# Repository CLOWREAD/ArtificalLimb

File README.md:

# ArtificalLimb
A repository to store data related to software and hardware design of a control card used to drive the solenoid for an artificial limb concept.

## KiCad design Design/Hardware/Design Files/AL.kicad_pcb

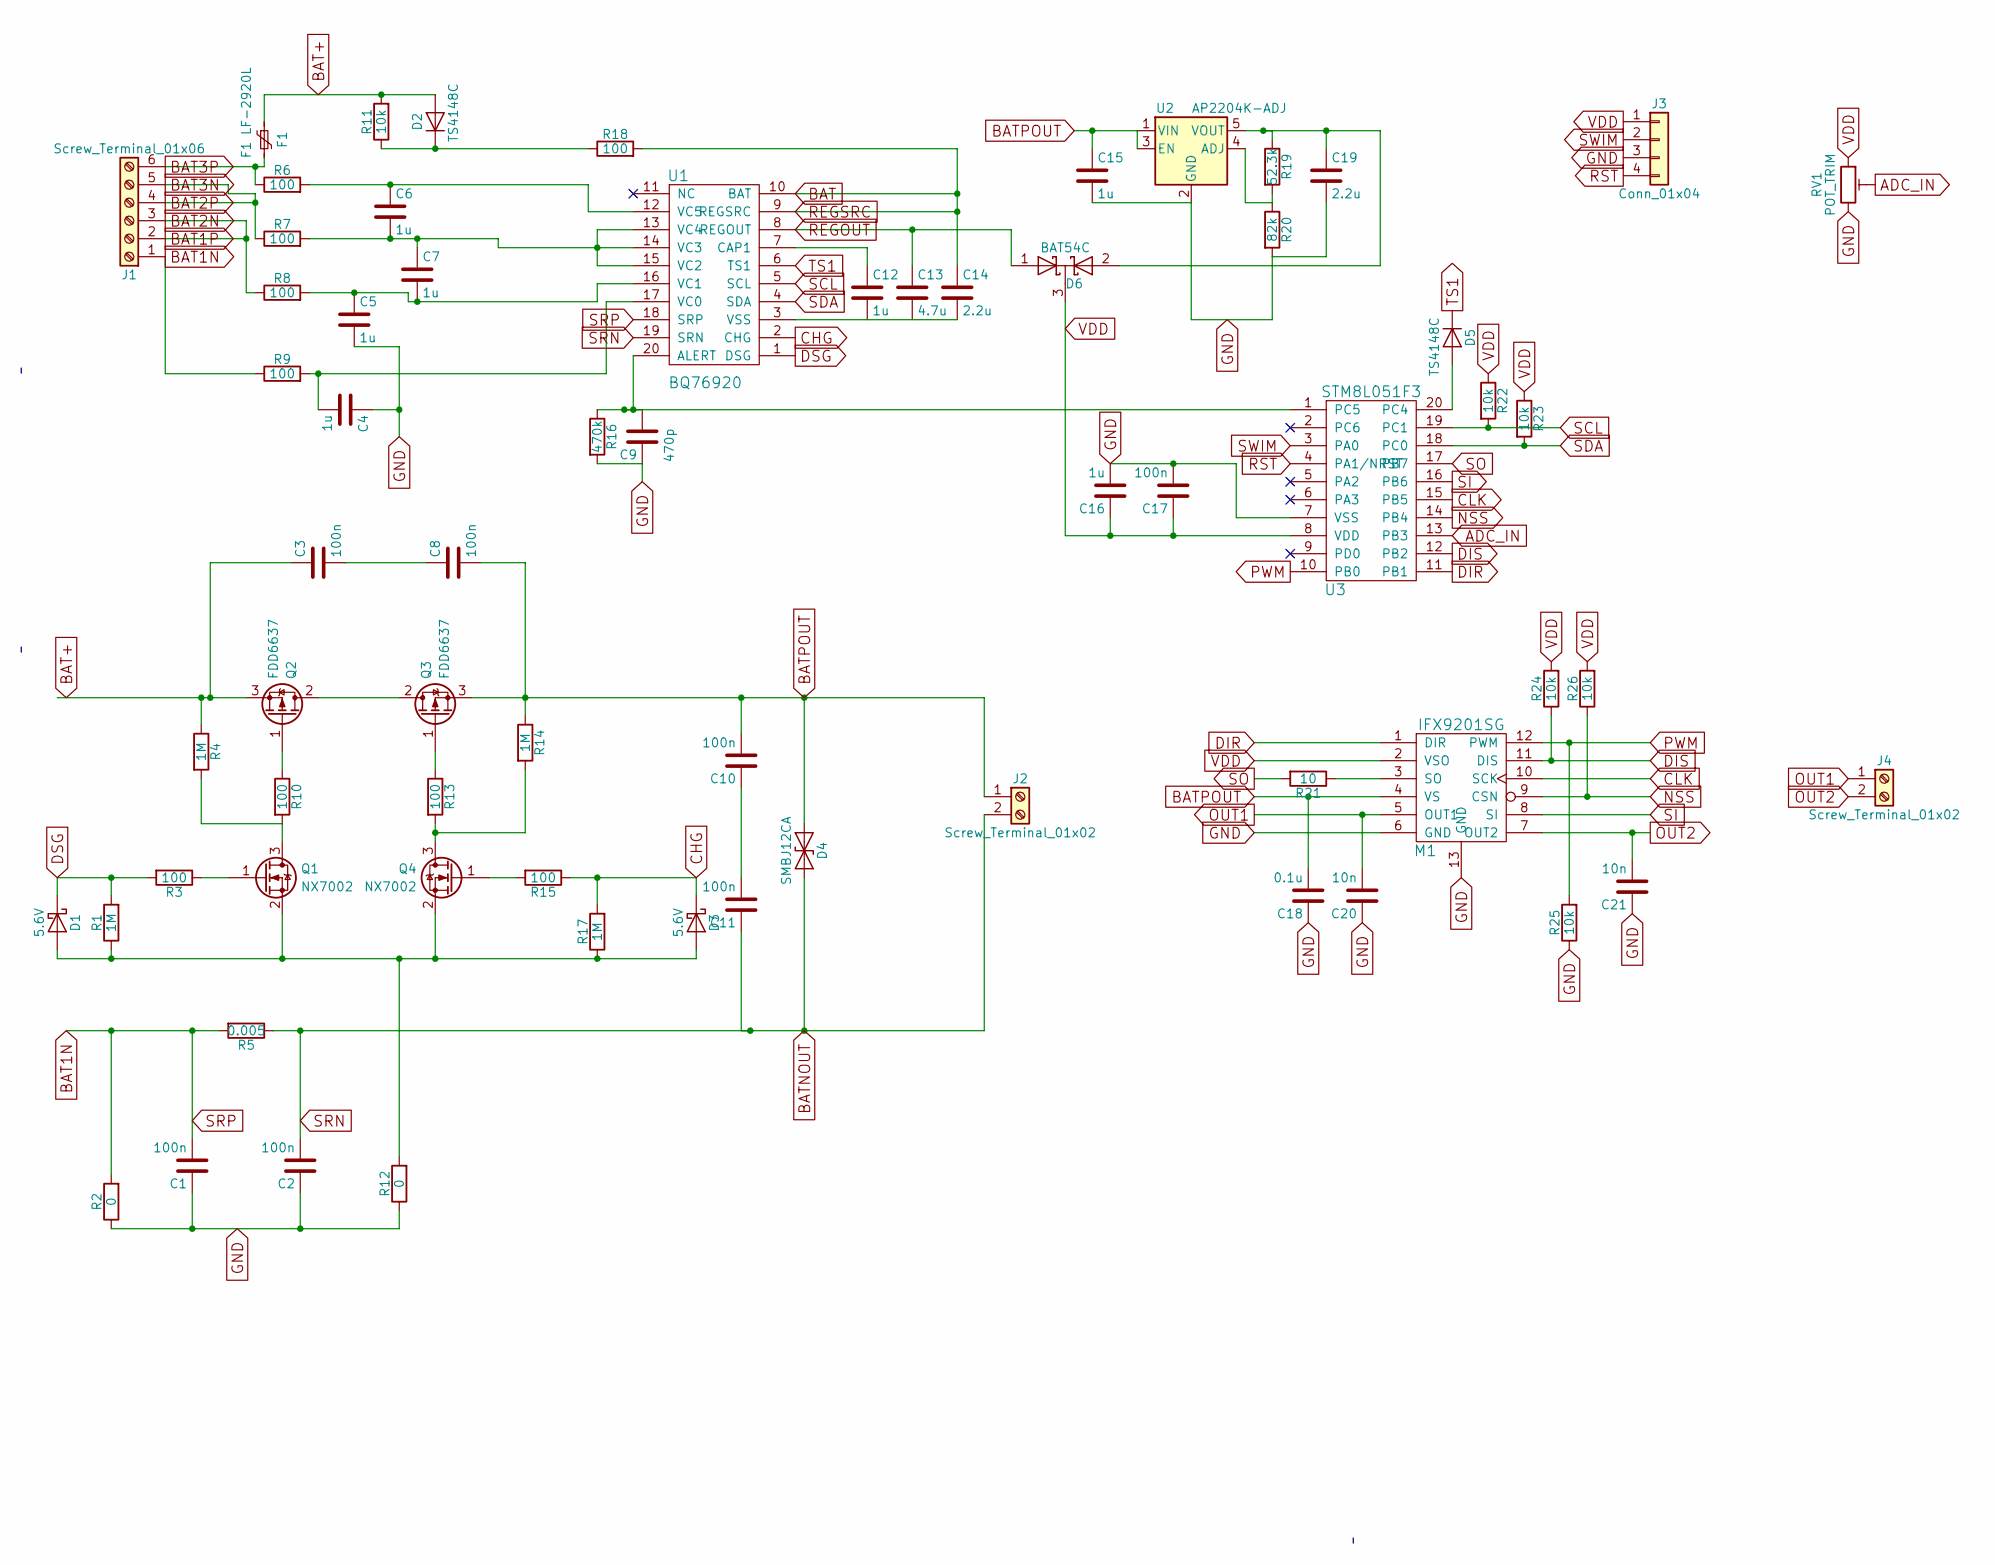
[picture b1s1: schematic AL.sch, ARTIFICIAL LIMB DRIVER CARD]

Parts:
C1, C2, C3, C8, C10, C11, C17: 100n; C_0603_HandSoldering
C4, C5, C6, C7, C12, C15, C16: 1u; C_0603_HandSoldering
C9: 470p; C_0603_HandSoldering
C13: 4.7u; C_0603_HandSoldering
C14, C19: 2.2u; C_0603_HandSoldering
C18: 0.1u; C_0603_HandSoldering
C20, C21: 10n; C_0603_HandSoldering
D1, D3: 5.6V
D2, D5: TS4148C; D_0603
D4: SMBJ12CA; DO214AA
D6: BAT54C; TSOT-23
F1: F1 LF-2920L; Fuse_SMD2920
J1: Screw_Terminal_01x06
J2, J4: Screw_Terminal_01x02
J3: Conn_01x04
M1: IFX9201SG; PG-DSO-12-17
Q1, Q4: NX7002; TSOT-23
Q2, Q3: FDD6637; TO-252-2
R1: 1M
R2, R12: 0; R_0805_HandSoldering
R3, R10, R15, R18: 100; R_0603_HandSoldering
R4, R14, R17: 1M; R_0603_HandSoldering
R5: 0.005; R_2512_HandSoldering
R6, R7, R8, R9: 100; R_1206
R11, R22, R23, R24, R25, R26: 10k; R_0603_HandSoldering
R13: 100
R16: 470k; R_0603_HandSoldering
R19: 52.3k; R_0603_HandSoldering
R20: 82k; R_0603_HandSoldering
R21: 10; R_0603_HandSoldering
RV1: POT_TRIM; Potentiometer_Trimmer_Bourns_3339P_Horizontal
U1: BQ76920; SSOP-20_4.4x6.5mm_Pitch0.65mm
U2: AP2204K-ADJ; SOT-23-5
U3: STM8L051F3; SSOP-20_4.4x6.5mm_Pitch0.65mm

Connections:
ADC_IN: RV1.2, U3.13 (PB3)
BAT: C14.1, R18.2, U1.9 (REGSRC), U1.10 (BAT)
BAT1N: C1.2, J1.1, R2.2, R5.2, R9.1, U1.18 (SRP)
BAT1P: J1.2, J1.3, R8.1
BAT2P: J1.4, J1.5, R7.1
BAT3P: F1.2, J1.6, R6.1
BAT+: C3.1, D2.2 (A), F1.1, Q2.3 (S), R4.1, R11.2
BATNOUT: C2.2, C11.1, D4.2 (A2), J2.2, R5.1, U1.19 (SRN)
BATPOUT: C8.2, C10.2, C15.1, C18.2, D4.1 (A1), J2.1, M1.4 (VS), Q3.3 (S), R14.1, U2.1 (VIN), U2.3 (EN)
CHG: D3.1 (K), R15.1, R17.2, U1.2 (CHG)
CLK: M1.10 (SCK), U3.15 (PB5)
DIR: M1.1 (DIR), U3.11 (PB1)
DIS: M1.11 (DIS), R24.1, U3.12 (PB2)
DSG: D1.1 (K), R1.2, R3.2, U1.1 (DSG)
GND: C1.1, C2.1, C4.1, C5.2, C9.1, C15.2, C16.2, C17.2, C18.1, C19.2, C20.1, C21.1, J3.3, M1.6 (GND), M1.13 (GND), R2.1, R12.1, R16.2, R20.2, R25.1, RV1.3, U2.2 (GND), U3.7 (VSS)
NSS: M1.9 (CSN), R26.1, U3.14 (PB4)
unnamed: C3.2, C8.1
unnamed: C4.2, R9.2, U1.17 (VC0)
unnamed: C5.1, C7.2, R8.2, U1.16 (VC1)
unnamed: C6.1, R6.2, U1.12 (VC5)
unnamed: C6.2, C7.1, R7.2, U1.13 (VC4), U1.14 (VC3), U1.15 (VC2)
unnamed: C9.2, R16.1, U1.20 (ALERT), U3.1 (PC5)
unnamed: C10.1, C11.2
unnamed: C12.1, U1.7 (CAP1)
unnamed: C14.2, U1.3 (VSS)
unnamed: C19.1, D6.2 (A), R19.1, U2.5 (VOUT)
unnamed: D1.2 (A), D3.2 (A), Q1.2 (S), Q4.2 (S), R1.1, R12.2, R17.1
unnamed: D2.1 (K), R11.1, R18.1
unnamed: D5.2 (A), U3.20 (PC4)
unnamed: M1.3 (SO), R21.1
unnamed: Q1.1 (G), R3.1
unnamed: Q1.3 (D), R4.2, R10.2
unnamed: Q2.1 (G), R10.1
unnamed: Q2.2 (D), Q3.2 (D)
unnamed: Q3.1 (G), R13.1
unnamed: Q4.1 (G), R15.2
unnamed: Q4.3 (D), R13.2, R14.2
unnamed: R19.2, R20.1, U2.4 (ADJ)
OUT1: C20.2, J4.1, M1.5 (OUT1)
OUT2: C21.2, J4.2, M1.7 (OUT2)
PWM: M1.12 (PWM), R25.2, U3.10 (PB0)
REGOUT: C13.1, D6.1 (A), U1.8 (REGOUT)
RST: J3.4, U3.4 (PA1/NRST)
SCL: R22.2, U1.5 (SCL), U3.19 (PC1)
SDA: R23.2, U1.4 (SDA), U3.18 (PC0)
SI: M1.8 (SI), U3.16 (PB6)
SO: R21.2, U3.17 (PB7)
SWIM: J3.2, U3.3 (PA0)
TS1: D5.1 (K), U1.6 (TS1)
VDD: C16.1, C17.1, D6.3 (K), J3.1, M1.2 (VSO), R22.1, R23.1, R24.2, R26.2, RV1.1, U3.8 (VDD)

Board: 2 copper layers, 62 parts (0 on the bottom side), 47 nets, no tracks yet.

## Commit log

2018-03-27 Added Structured File System, KiCAD PCB Design Files, Datasheets, updated BOM and Schematic.
2018-04-07 Schematic Update
2018-04-08 Updated date and credentials
